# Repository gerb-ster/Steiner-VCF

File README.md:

# YUSynth Steiner VCF

Another one of the wonderful VCF designs from YuSynth. The VCF ‘core’ is the same as the design from YuSynth, I just replaced the rotary switch with a ‘digital’ version controlled by a Atmel ATTINY22 and a ADG412 digital SPST switch. This allows you to select 2 more modes, namely HP+BP and LP+BP, next to HP, BP, LP and AP (LP+BP+HP).

The original design:

http://yusynth.net/Modular/EN/STEINERVCF/index-v2.html

## Status: Work in Progress

- done: first schematic & board design
- done: breadboard and test
- done: design frontpanel
- done: order PCB and build prototype
- todo: final debugging
- todo: rewrite the firmware in pure C

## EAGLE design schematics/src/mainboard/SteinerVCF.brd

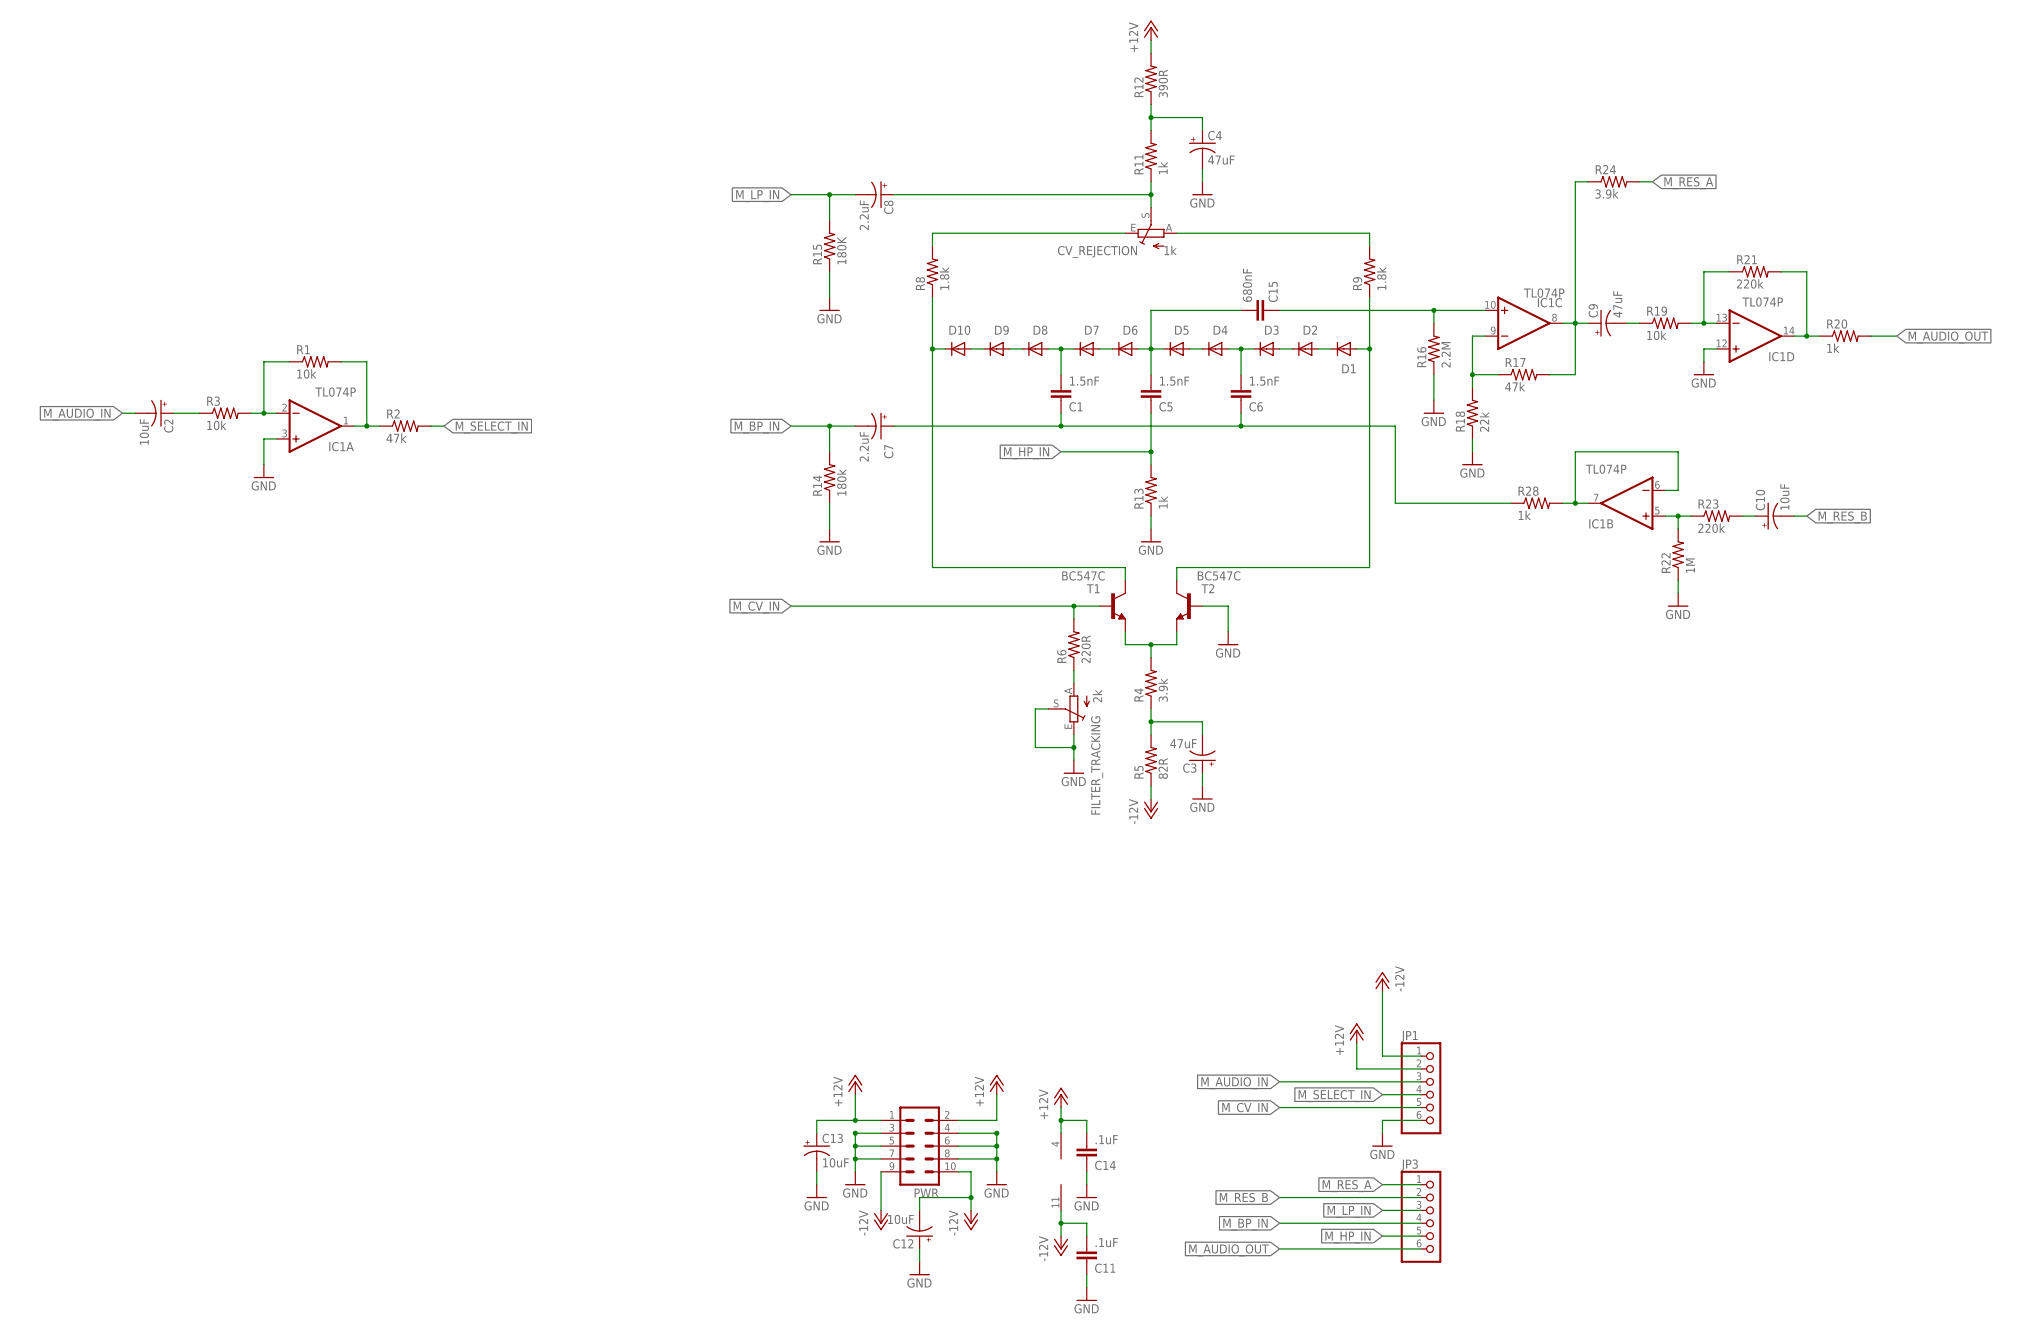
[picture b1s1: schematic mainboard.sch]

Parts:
C1, C5, C6: 1.5nF; C050-024X044
C2, C10, C12, C13: 10uF; E2,5-5
C3, C4, C9: 47uF; E2,5-5
C7, C8: 2.2uF; E2,5-5
C11, C14: .1uF; C050-024X044
C15: 680nF; C050-035X075
CV_REJECTION: 1k; S64YW
D1, D2, D3, D4, D5, D6, D7, D8, D9, D10: 1N4148DO35-7; DO35-7
FILTER_TRACKING: 2k; S64YW
IC1: TL074P; DIL14
JP1, JP3: PINHD-1X6; 1X06
PWR: ML10
R1, R3, R19: 10k; 0204/7
R2, R17: 47k; 0204/7
R4, R24: 3.9k; 0204/7
R5: 82R; 0204/7
R6: 220R; 0204/7
R8, R9: 1.8k; 0204/7
R11, R13, R20, R28: 1k; 0204/7
R12: 390R; 0204/7
R14: 180k; 0204/7
R15: 180K; 0204/7
R16: 2.2M; 0204/7
R18: 22k; 0204/7
R21, R23: 220k; 0204/7
R22: 1M; 0204/7
T1, T2: BC547C; TO92-CBE

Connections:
+12V: C13.+, C14.1, IC1.4 (V+), JP1.2, PWR.1, PWR.2, R12.2
-12V: C11.1, C12.-, IC1.11 (V-), JP1.1, PWR.9, PWR.10, R5.1
GND: C3.+, C4.-, C11.2, C12.+, C13.-, C14.2, FILTER_TRACKING.E, FILTER_TRACKING.S, IC1.3 (+IN), IC1.12 (+IN), JP1.6, PWR.3, PWR.4, PWR.5, PWR.6, PWR.7, PWR.8, R13.1, R14.1, R15.1, R16.1, R18.1, R22.1, T2.B
M_AUDIO_IN: C2.-, JP1.3
M_AUDIO_OUT: JP3.6, R20.2
M_BP_IN: C7.-, JP3.4, R14.2
M_CV_IN: JP1.5, R6.2, T1.B
M_HP_IN: C5.2, JP3.5, R13.2
M_LP_IN: C8.-, JP3.3, R15.2
M_RES_A: JP3.1, R24.2
M_RES_B: C10.-, JP3.2
M_SELECT_IN: JP1.4, R2.2
unnamed: C2.+, R3.1
unnamed: IC1.2 (-IN), R1.1, R3.2
unnamed: IC1.1 (OUT), R1.2, R2.1
unnamed: C3.-, R4.1, R5.2
unnamed: R4.2, T1.E, T2.E
unnamed: D1.A, R9.1, T2.C
unnamed: FILTER_TRACKING.A, R6.1
unnamed: D10.C, R8.1, T1.C
unnamed: D9.C, D10.A
unnamed: D8.C, D9.A
unnamed: C1.1, D7.C, D8.A
unnamed: D6.C, D7.A
unnamed: C15.2, IC1.10 (+IN), R16.2
unnamed: D4.C, D5.A
unnamed: C6.1, D3.C, D4.A
unnamed: D2.C, D3.A
unnamed: D1.C, D2.A
unnamed: CV_REJECTION.E, R8.2
unnamed: CV_REJECTION.A, R9.2
unnamed: C8.+, CV_REJECTION.S, R11.1
unnamed: C4.+, R11.2, R12.1
unnamed: C1.2, C6.2, C7.+, R28.1
unnamed: IC1.9 (-IN), R17.1, R18.2
unnamed: C9.+, IC1.8 (OUT), R17.2, R24.1
unnamed: IC1.13 (-IN), R19.2, R21.1
unnamed: C9.-, R19.1
unnamed: IC1.5 (+IN), R22.2, R23.1
unnamed: IC1.14 (OUT), R20.1, R21.2
unnamed: C10.+, R23.2
unnamed: IC1.6 (-IN), IC1.7 (OUT), R28.2
unnamed: C5.1, C15.1, D5.C, D6.A

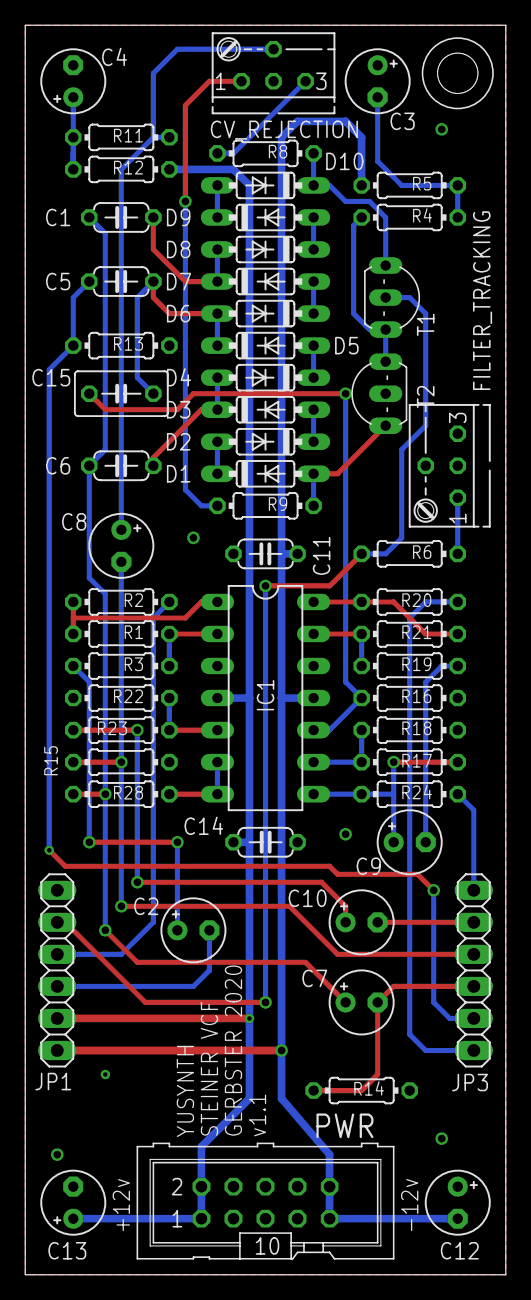
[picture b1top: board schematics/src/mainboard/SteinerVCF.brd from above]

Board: 2 copper layers, 38.1 x 99.1 mm, 56 parts (0 on the bottom side), 43 nets.

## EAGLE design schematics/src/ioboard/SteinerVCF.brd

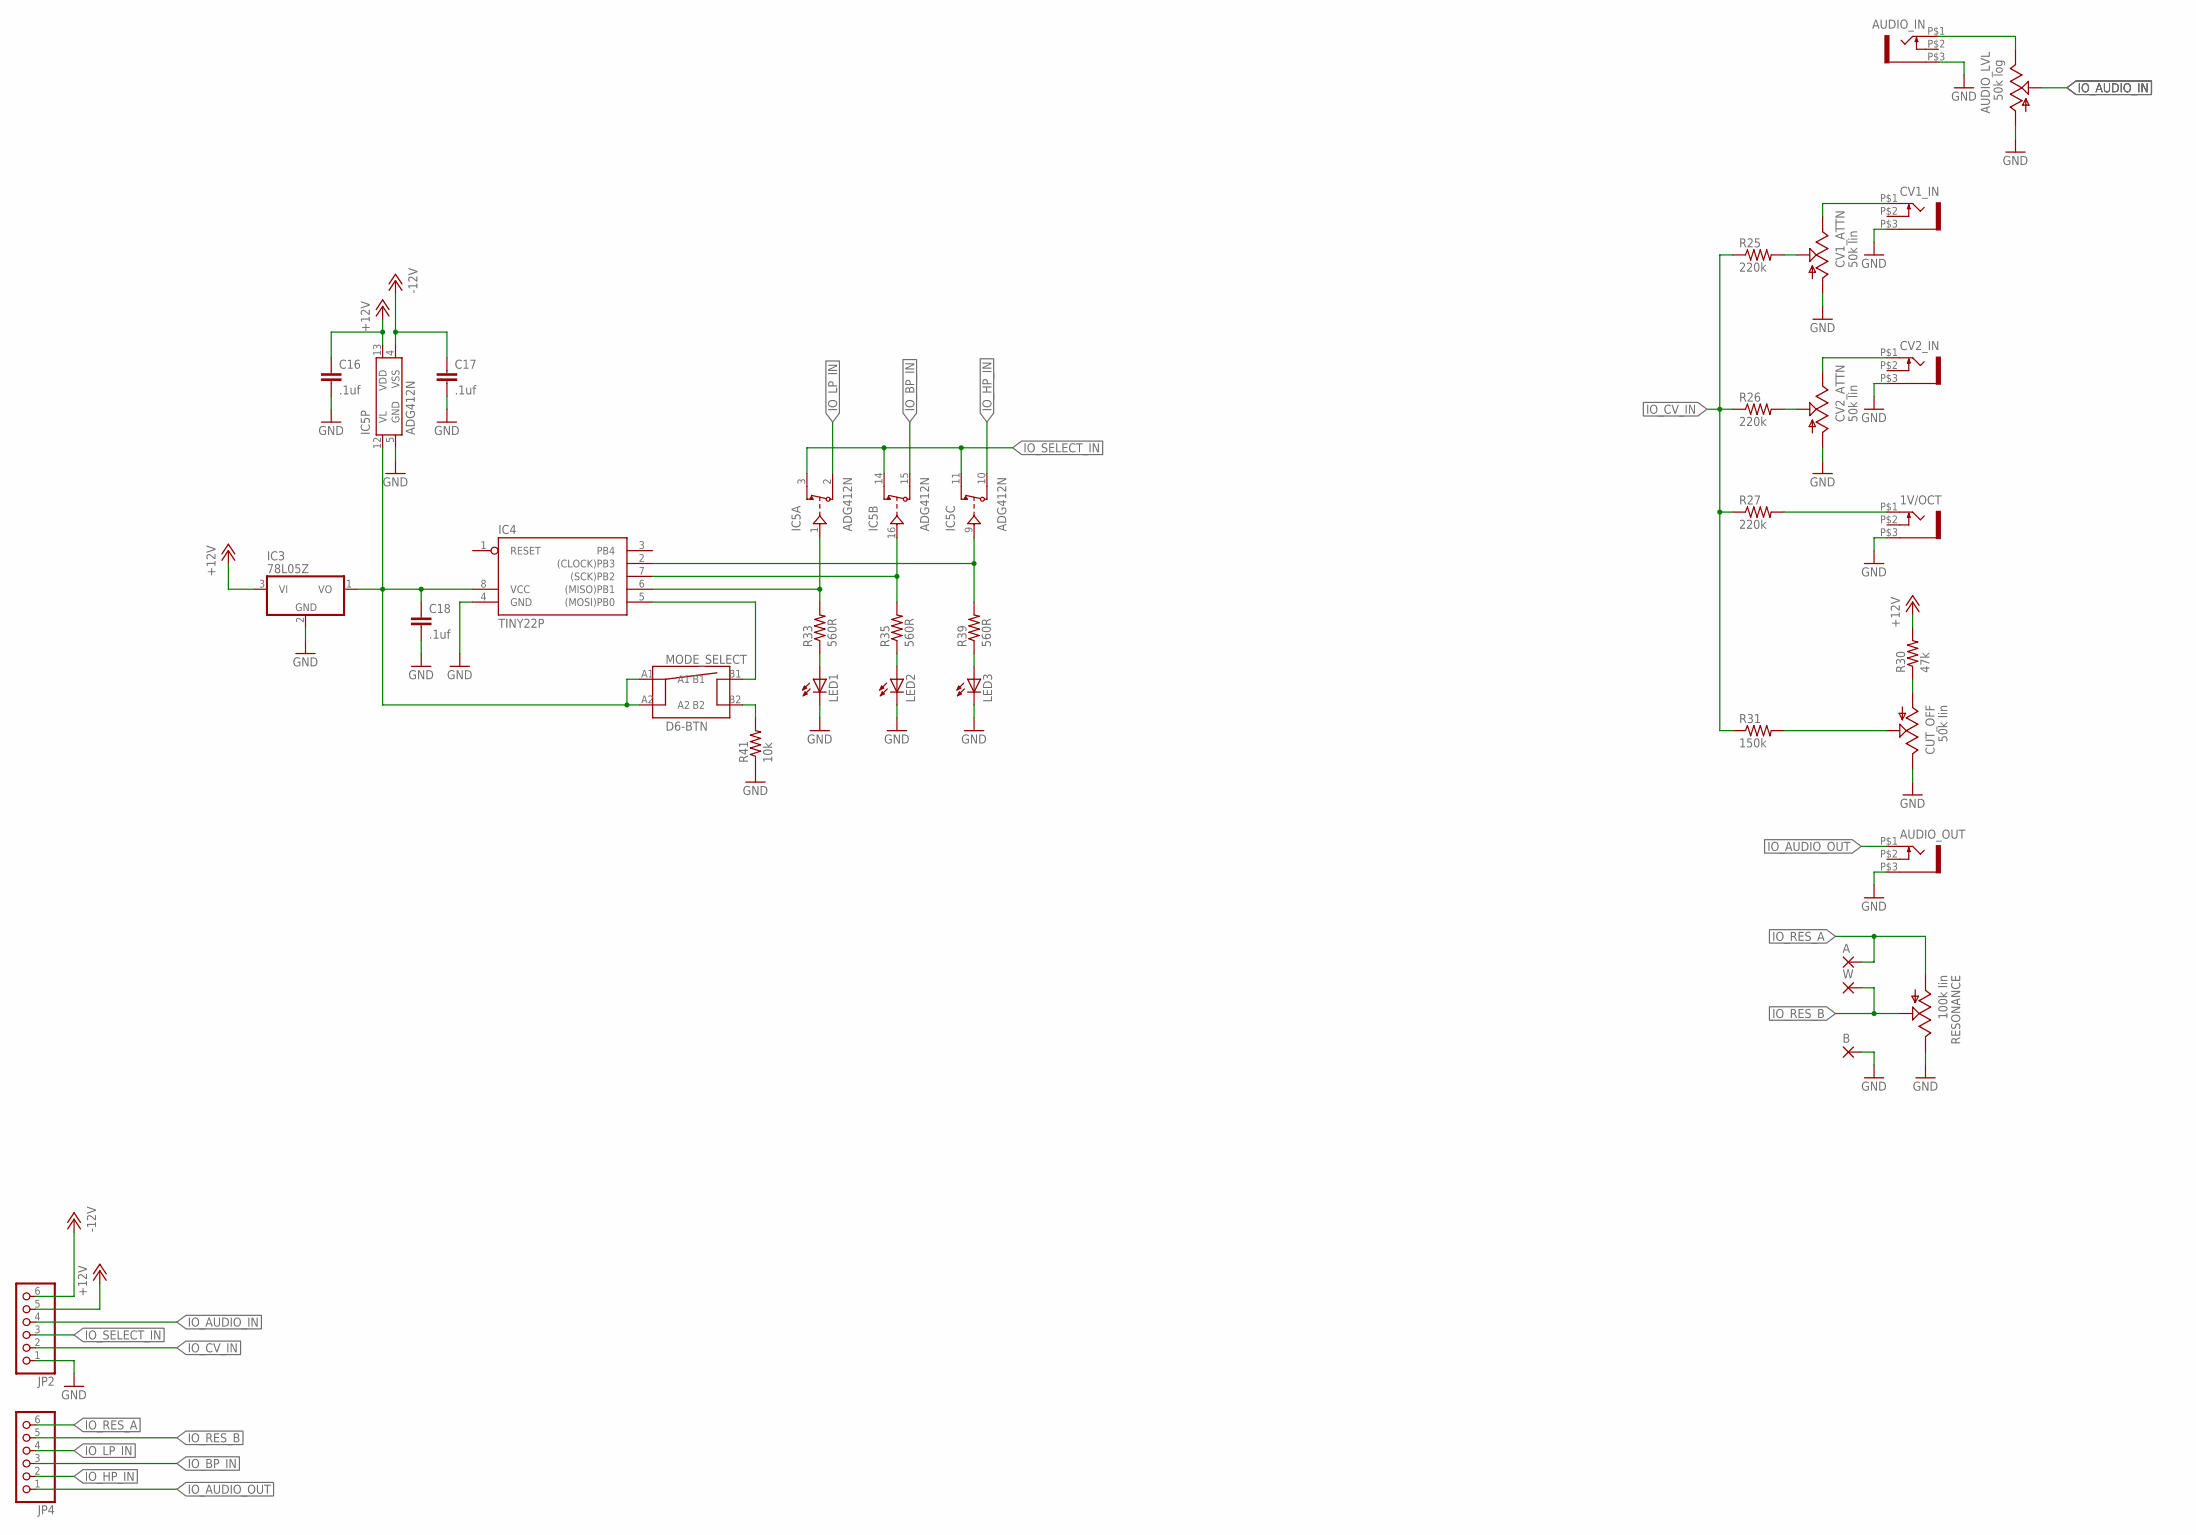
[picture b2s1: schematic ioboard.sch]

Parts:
1V/OCT: WQP-PJ301M-12_JACK
A: 2,15/1,0
AUDIO_IN: WQP-PJ301M-12_JACK
AUDIO_LVL: 50k log; EVUF
AUDIO_OUT: WQP-PJ301M-12_JACK
B: 2,15/1,0
C16, C17, C18: .1uf; C050-024X044
CUT_OFF: 50k lin; EVUF
CV1_ATTN, CV2_ATTN: 50k lin; EVUF
CV1_IN, CV2_IN: WQP-PJ301M-12_JACK
IC3: 78L05Z; TO92
IC4: TINY22P; DIL08
IC5: ADG412N; DIL16
JP2, JP4: PINHD-1X6; 1X06
LED1, LED2, LED3: LED3MM
MODE_SELECT: D6-BTN
R25, R26, R27: 220k; 0204/7
R30: 47k; 0204/7
R31: 150k; 0204/7
R33, R35, R39: 560R; 0207/7
R41: 10k; 0207/7
RESONANCE: 100k lin; EVUF
W: 2,15/1,0

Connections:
+12V: C16.1, IC3.3 (VI), IC5.13 (VDD), JP2.5, R30.2
-12V: C17.1, IC5.4 (VSS), JP2.6
GND: 1V/OCT.P$3 (1), AUDIO_IN.P$3 (1), AUDIO_LVL.1 (A), AUDIO_OUT.P$3 (1), B.1, C16.2, C17.2, C18.2, CUT_OFF.3 (E), CV1_ATTN.1 (A), CV1_IN.P$3 (1), CV2_ATTN.1 (A), CV2_IN.P$3 (1), IC3.2 (GND), IC4.4 (GND), IC5.5 (GND), JP2.1, LED1.K (C), LED2.K (C), LED3.K (C), R41.1, RESONANCE.3 (E)
IO_A: IC4.6 ((MISO)PB1), IC5.1 (IN), R33.2
IO_AUDIO_IN: AUDIO_LVL.2 (S), JP2.4
IO_AUDIO_OUT: AUDIO_OUT.P$1 (2), JP4.1
IO_B: IC4.7 ((SCK)PB2), IC5.16 (IN), R35.2
IO_BP_IN: IC5.15 (D), JP4.3
IO_CV_IN: JP2.2, R25.1, R26.1, R27.1, R31.1
IO_HP_IN: IC5.10 (D), JP4.2
IO_LP_IN: IC5.2 (D), JP4.4
IO_RES_A: A.1, JP4.6, RESONANCE.1 (A)
IO_RES_B: JP4.5, RESONANCE.2 (S), W.1
IO_SELECT_IN: IC5.3 (S), IC5.11 (S), IC5.14 (S), JP2.3
unnamed: MODE_SELECT.B2, R41.2
unnamed: C18.1, IC3.1 (VO), IC4.8 (VCC), IC5.12 (VL), MODE_SELECT.A1, MODE_SELECT.A2
unnamed: IC4.2 ((CLOCK)PB3), IC5.9 (IN), R39.2
unnamed: AUDIO_IN.P$1 (2), AUDIO_LVL.3 (E)
unnamed: LED1.A, R33.1
unnamed: CV1_ATTN.2 (S), R25.2
unnamed: CV2_ATTN.2 (S), R26.2
unnamed: CV1_ATTN.3 (E), CV1_IN.P$1 (2)
unnamed: LED2.A, R35.1
unnamed: LED3.A, R39.1
unnamed: CV2_ATTN.3 (E), CV2_IN.P$1 (2)
unnamed: IC4.5 ((MOSI)PB0), MODE_SELECT.B1
unnamed: CUT_OFF.1 (A), R30.1
unnamed: 1V/OCT.P$1 (2), R27.2
unnamed: CUT_OFF.2 (S), R31.2

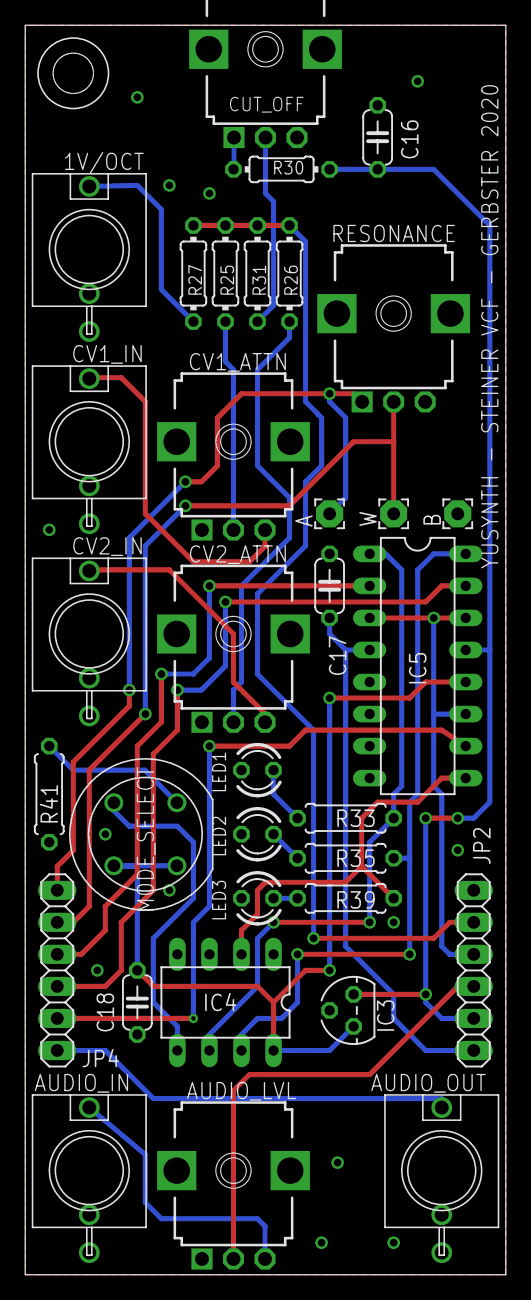
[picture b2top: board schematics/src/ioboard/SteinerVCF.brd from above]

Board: 2 copper layers, 38.1 x 99.1 mm, 34 parts (0 on the bottom side), 29 nets.

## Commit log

2021-05-06 some files
2021-05-07 Added files & structure
2021-05-10 Added Status
2021-05-10 Added firmware
2021-05-11 Added Status & Images
2021-08-06 Updated some schematics and docs
2021-08-10 Fixed some bugs and updated documentation
2022-04-20 Some updates & bugfixes
2022-04-22 Fixed schematics & descriptions
2022-05-17 Updated Firmware
2022-05-18 Updated Faceplates
2022-05-18 Fixed issues
2022-05-21 Fixed schematics
2022-05-28 General updates
